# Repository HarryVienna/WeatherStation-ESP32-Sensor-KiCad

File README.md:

# Weather station

### Build your own Raspberry Pi weather station with weather forecast and ESP32 wireless sensors

You can find a detailed description on [my website](https://www.haraldkreuzer.net/en/news/build-your-own-raspberry-pi-weather-station-weather-forecast-and-esp32-wireless-sensors)

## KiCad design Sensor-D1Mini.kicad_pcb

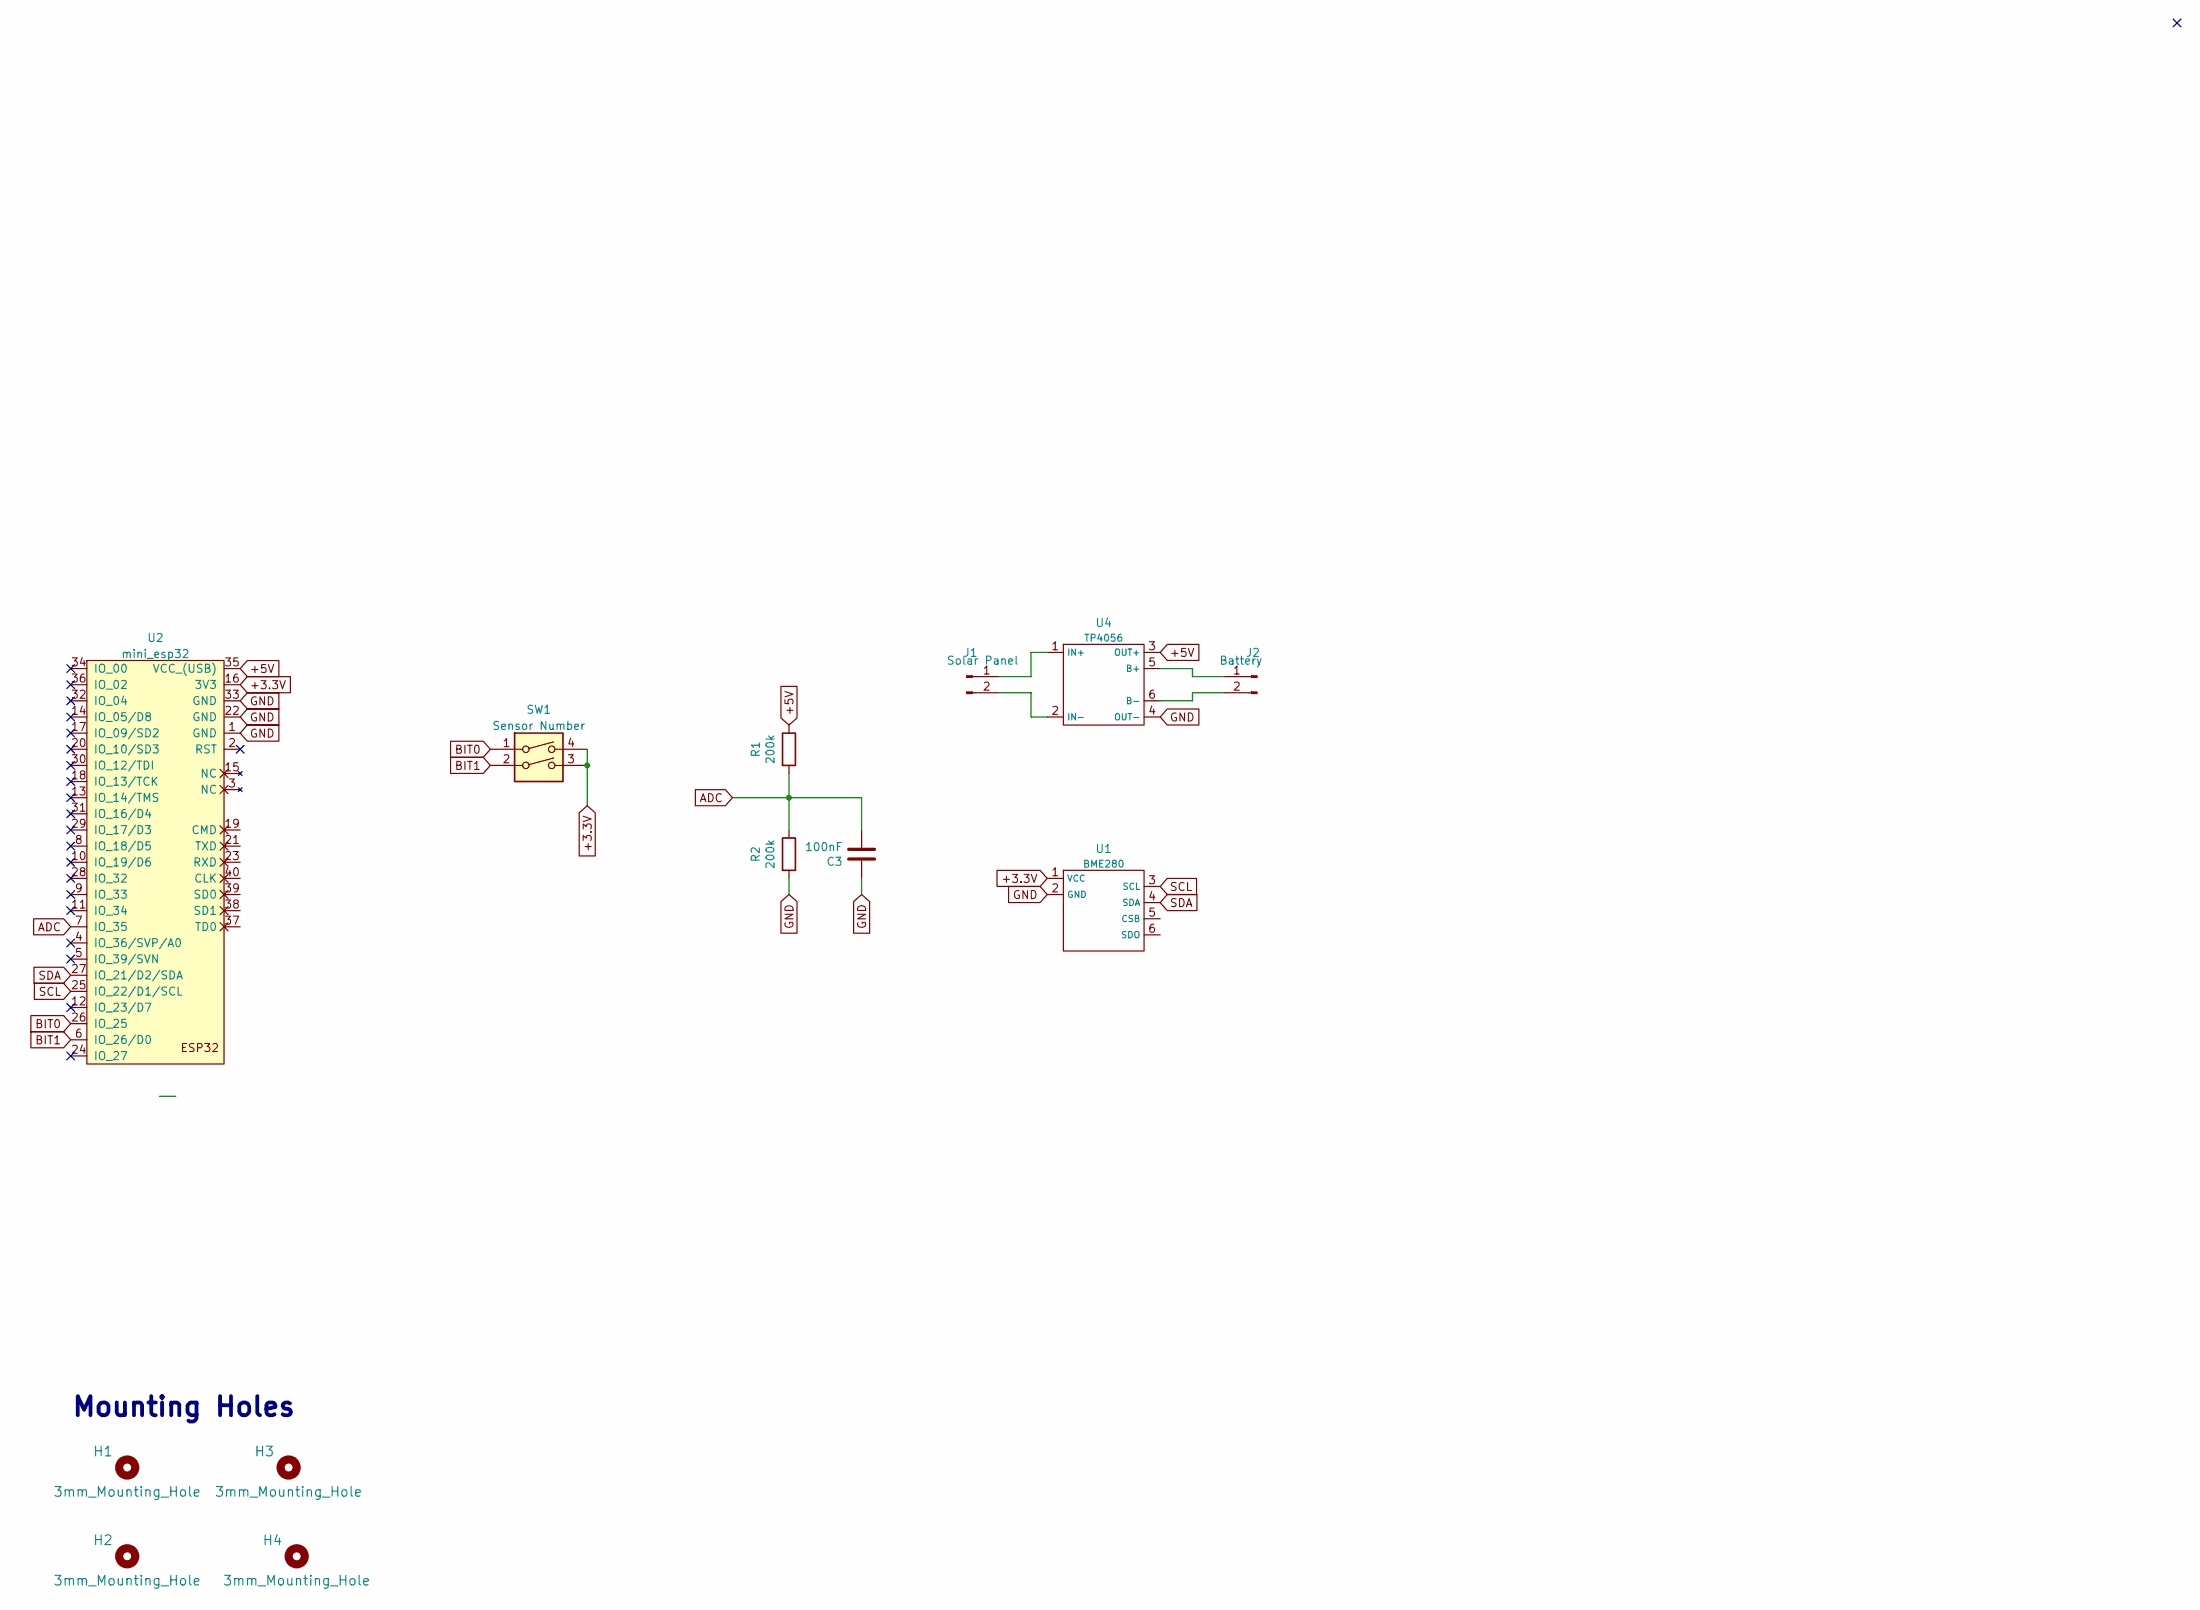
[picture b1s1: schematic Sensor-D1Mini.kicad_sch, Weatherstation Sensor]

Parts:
C3: 100nF; C_Disc_D7.0mm_W2.5mm_P5.00mm
H1, H2, H3, H4: 3mm_Mounting_Hole; NPTH_3mm_ID
J1: Solar Panel; JST_PH_B2B-PH-K_1x02_P2.00mm_Vertical
J2: Battery; JST_PH_B2B-PH-K_1x02_P2.00mm_Vertical
R1, R2: 200k; R_Axial_DIN0207_L6.3mm_D2.5mm_P10.16mm_Horizontal
SW1: Sensor Number; DIP-4_W7.62mm
U1: BME280; BME280-Module
U2: mini_esp32; ESP32_mini
U4: TP4056; TP4056-Module

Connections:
+3.3V: SW1.3, SW1.4, U1.1 (VCC), U2.16 (3V3)
+5V: R1.1, U2.35 (VCC_(USB)), U4.3 (OUT+)
ADC: C3.2, R1.2, R2.1, U2.7 (IO_35)
BIT0: SW1.1, U2.26 (IO_25)
BIT1: SW1.2, U2.6 (IO_26/D0)
GND: C3.1, R2.2, U1.2 (GND), U2.1 (GND), U2.22 (GND), U2.33 (GND), U4.4 (OUT-)
unnamed: J1.1, U4.1 (IN+)
unnamed: J1.2, U4.2 (IN-)
unnamed: J2.1, U4.5 (B+)
unnamed: J2.2, U4.6 (B-)
SCL: U1.3 (SCL), U2.25 (IO_22/D1/SCL)
SDA: U1.4 (SDA), U2.27 (IO_21/D2/SDA)

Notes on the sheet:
Mounting Holes

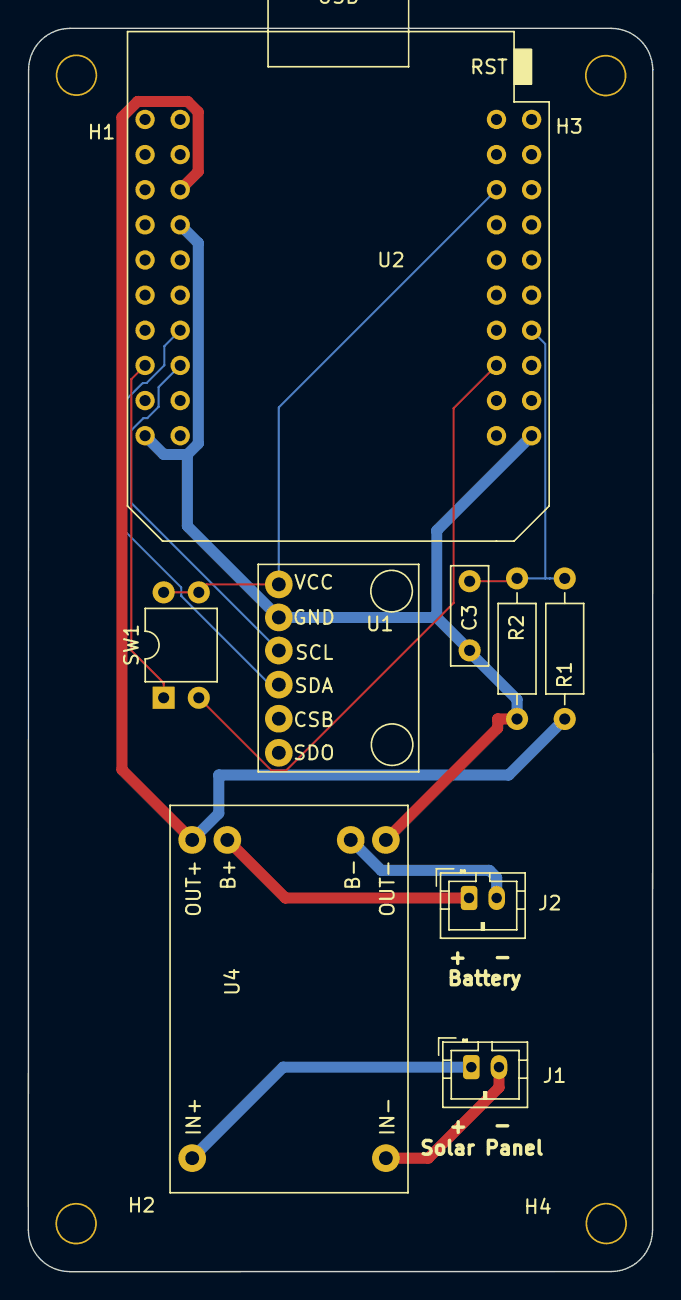
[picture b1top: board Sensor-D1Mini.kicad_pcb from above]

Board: 2 copper layers, 45.1 x 89.9 mm, 13 parts (0 on the bottom side), 12 nets.

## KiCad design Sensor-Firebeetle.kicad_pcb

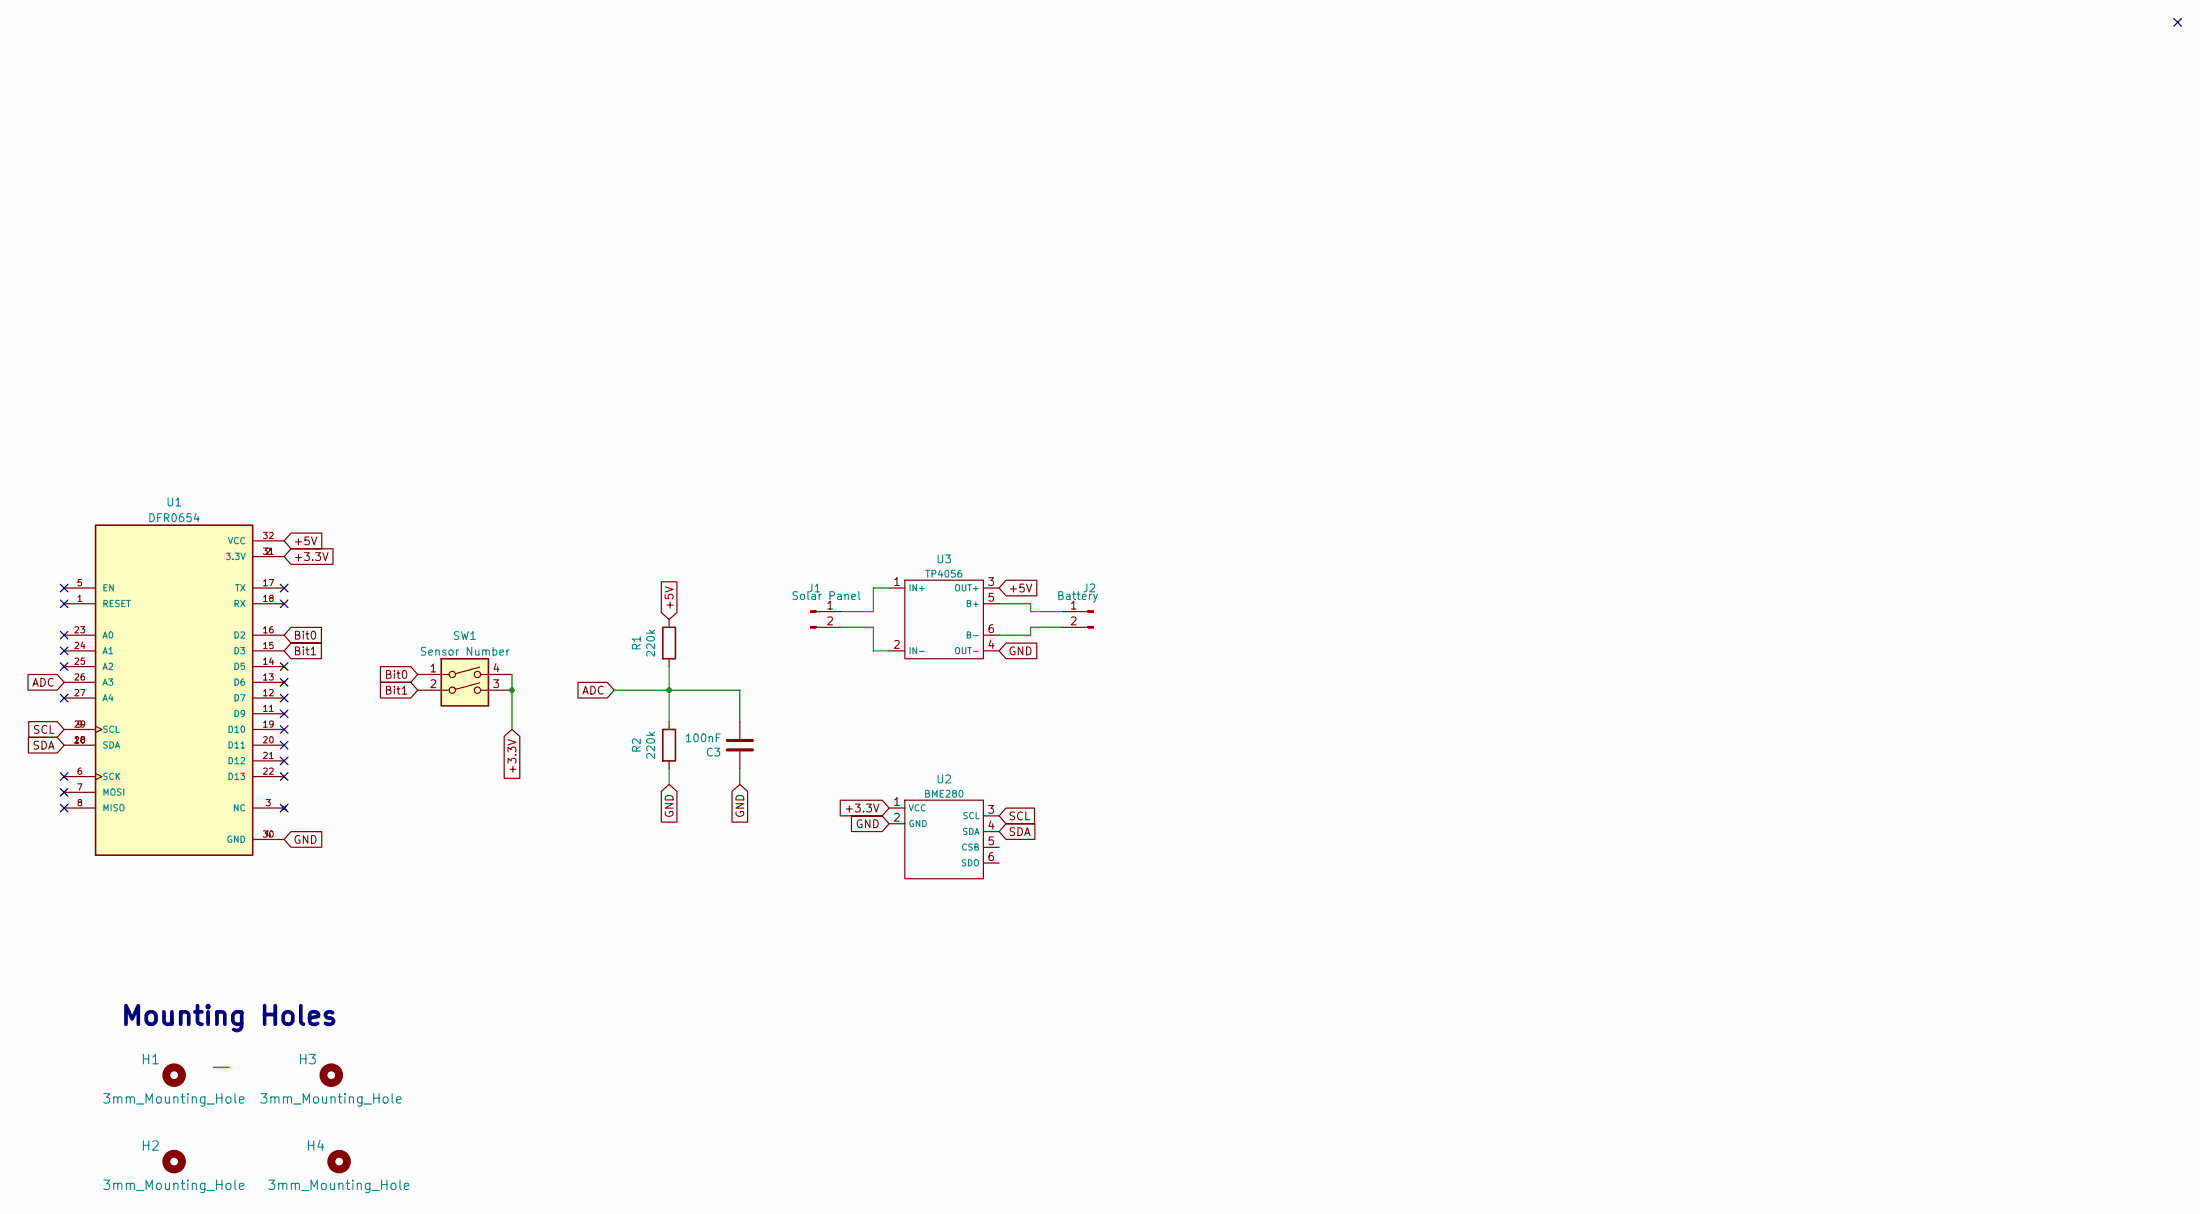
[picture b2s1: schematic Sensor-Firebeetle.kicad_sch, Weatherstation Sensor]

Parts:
C3: 100nF; C_Disc_D7.0mm_W2.5mm_P5.00mm
H1, H2, H3, H4: 3mm_Mounting_Hole; NPTH_3mm_ID
J1: Solar Panel; JST_PH_B2B-PH-K_1x02_P2.00mm_Vertical
J2: Battery; JST_PH_B2B-PH-K_1x02_P2.00mm_Vertical
R1, R2: 220k; R_Axial_DIN0207_L6.3mm_D2.5mm_P10.16mm_Horizontal
SW1: Sensor Number; DIP-4_W7.62mm
U1: DFR0654; MODULE_DFR0654
U2: BME280; BME280-Module
U3: TP4056; TP4056-Module

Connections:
+3.3V: SW1.3, SW1.4, U1.2 (3.3V), U1.31 (3.3V), U2.1 (VCC)
+5V: R1.1, U1.32 (VCC), U3.3 (OUT+)
ADC: C3.2, R1.2, R2.1, U1.26 (A3)
Bit0: SW1.1, U1.16 (D2)
Bit1: SW1.2, U1.15 (D3)
GND: C3.1, R2.2, U1.4 (GND), U1.30 (GND), U2.2 (GND), U3.4 (OUT-)
unnamed: J1.1, U3.1 (IN+)
unnamed: J1.2, U3.2 (IN-)
unnamed: J2.1, U3.5 (B+)
unnamed: J2.2, U3.6 (B-)
SCL: U1.9 (SCL), U1.29 (SCL), U2.3 (SCL)
SDA: U1.10 (SDA), U1.28 (SDA), U2.4 (SDA)

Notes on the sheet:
Mounting Holes

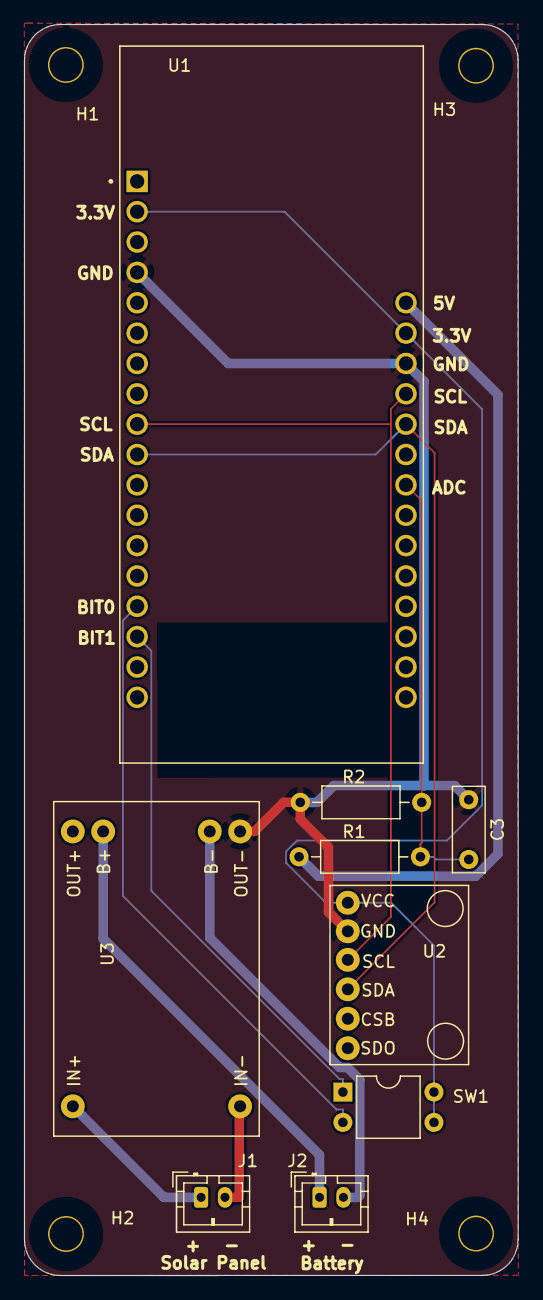
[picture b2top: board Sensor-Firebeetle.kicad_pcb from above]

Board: 2 copper layers, 41.3 x 104.7 mm, 13 parts (0 on the bottom side), 12 nets.

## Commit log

2022-12-20 3.3V for switches
